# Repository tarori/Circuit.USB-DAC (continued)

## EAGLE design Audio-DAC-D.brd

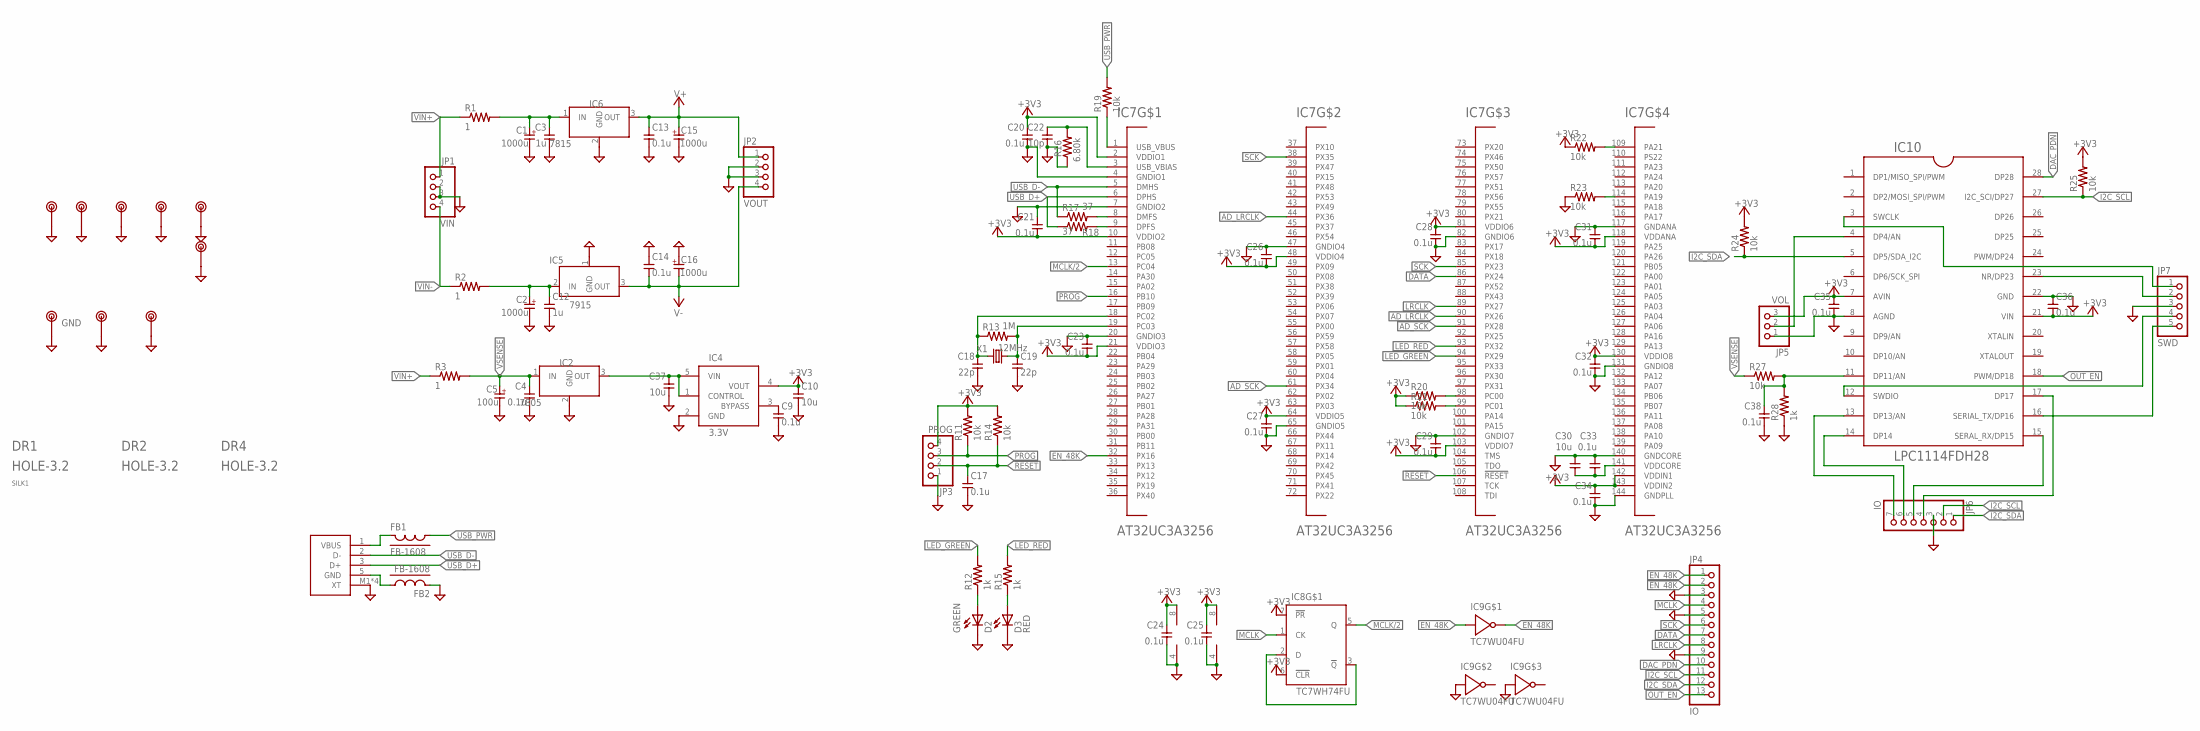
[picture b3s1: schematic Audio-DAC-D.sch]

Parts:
C1, C2, C15, C16: 1000u; E5-10
C3, C12: 1u; 1608
C4, C9, C17, C20, C21, C23, C24, C25, C26, C27, C28, C29, C31, C32, C33, C34, C35, C36, C38: 0.1u; 1608
C5: 100u; E2.5-6.5
C10, C30, C37: 10u; 2012
C13, C14: 0.1u; 2012
C18, C19: 22p; 1608
C22: 10p; 1608
CON1: USB; UX60A-MB-5ST
D2: GREEN; D1608
D3: RED; D1608
DR1, DR2, DR4: HOLE-3.2; HOLE_3.2
FB1, FB2: FB-1608; 1608
IC2: 7805; 7805-LARGEHOLE
IC4: 3.3V; SOT23-5
IC5: 7915; 7805-LARGEHOLE
IC6: 7815; 7805-LARGEHOLE
IC7: AT32UC3A3256; TQFP144
IC8: TC7WH74FU; SSOP8-P-0.65
IC9: TC7WU04FU; SSOP8-P-0.65
IC10: LPC1114FDH28; TSSOP28
JP1: VIN; 1X04
JP2: VOUT; 1X04
JP3: PROG; 1X04
JP4: IO; 1X13
JP5: VOL; 1X03
JP6: IO; 1X07
JP7: SWD; 1X05
R1, R2, R3: 1; 0204/7
R11, R14, R19, R20, R21, R22, R23, R24, R25, R27: 10k; 1608
R12, R15, R28: 1k; 1608
R13: 1M; 0204/7
R16: 6.80k; 1608
R17, R18: 37; 1608
SILK1: ROBOTECHWHEELSILK-9MM; ROBOTECHWHEEL-9MM
TP1, TP3, TP4, TP5, TP6, TP7, TP8, TP9: TESTPIN
TP2: GND; TESTPIN
X1: 12MHz; HC49/S

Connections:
!EN_48K: IC9.7, JP4.2
!RESET: C17.1, IC7.106 (!RESET), JP3.2, R14.1
+3V3: C10.1, C20.1, C21.2, C23.2, C24.1, C25.1, C26.2, C27.1, C28.1, C29.2, C31.2, C32.1, C34.1, C35.1, C36.2, IC4.4 (VOUT), IC7.2 (VDDIO1), IC7.10 (VDDIO2), IC7.21 (VDDIO3), IC7.48 (VDDIO4), IC7.64 (VDDIO5), IC7.81 (VDDIO6), IC7.103 (VDDIO7), IC7.118 (VDDANA), IC7.130 (VDDIO8), IC7.142 (VDDIN1), IC7.143 (VDDIN2), IC8.6 (!CLR), IC8.7 (!PR), IC8.8 (V+), IC9.8 (V+), IC10.7 (AVIN), IC10.21 (VIN), JP3.4, JP5.3, R11.2, R14.2, R20.1, R21.1, R22.1, R24.2, R25.2
AD_LRCLK: IC7.44 (PX36), IC7.90 (PX26)
AD_SCK: IC7.61 (PX34), IC7.91 (PX28)
DAC_PDN: IC10.28 (DP28), JP4.10
DATA: IC7.86 (PX24), JP4.7
EN_48K: IC7.32 (PX16), IC9.1, JP4.1
GND: C1.- (2), C2.- (2), C3.2, C4.2, C5.- (2), C9.2, C10.2, C12.2, C13.2, C14.1, C15.- (2), C16.+ (1), C17.2, C18.2, C19.2, C20.2, C21.1, C22.2, C23.1, C24.2, C25.2, C26.1, C27.2, C28.2, C29.1, C30.1, C31.1, C32.2, C33.1, C34.2, C35.2, C36.1, C37.2, C38.2, CON1.M1 (XT), CON1.M2 (XT), CON1.M3 (XT), CON1.M4 (XT), D2.K, D3.K, FB2.2, IC2.2 (GND), IC4.2 (GND), IC5.1 (GND), IC6.2 (GND), IC7.4 (GNDIO1), IC7.7 (GNDIO2), IC7.20 (GNDIO3), IC7.47 (GNDIO4), IC7.65 (GNDIO5), IC7.82 (GNDIO6), IC7.102 (GNDIO7), IC7.117 (GNDANA), IC7.131 (GNDIO8), IC7.140 (GNDCORE), IC7.144 (GNDPLL), IC8.4 (V-), IC9.3, IC9.4 (V-), IC9.6, IC10.8 (AGND), IC10.22 (GND), JP1.2, JP1.3, JP2.2, JP2.3, JP3.1, JP4.3, JP4.5, JP4.9, JP5.1, JP6.3, JP7.3, R16.1, R23.1, R28.1, TP1.1, TP2.1, TP3.1, TP4.1, TP5.1, TP6.1, TP7.1, TP8.1, TP9.1
I2C_SCL: IC10.27 (I2C_SCI/DP27), JP4.11, JP6.2, R25.1
I2C_SDA: IC10.5 (DP5/SDA_I2C), JP4.12, JP6.1, R24.1
LED_GREEN: IC7.94 (PX29), R12.2
LED_RED: IC7.93 (PX32), R15.2
LRCLK: IC7.89 (PX27), JP4.8
MCLK: IC8.1 (CK), JP4.4
MCLK/2: IC7.13 (PC04), IC8.5 (Q)
unnamed: CON1.5 (GND), FB2.1
unnamed: IC10.4 (DP4/AN), JP5.2
unnamed: C9.1, IC4.3 (BYPASS)
unnamed: C37.1, IC2.3 (OUT), IC4.1 (CONTROL), IC4.5 (VIN)
unnamed: IC7.9 (DPFS), R18.2
unnamed: IC7.8 (DMFS), R17.2
unnamed: C22.1, IC7.3 (USB_VBIAS), R16.2
unnamed: C19.1, IC7.19 (PC03), R13.2, X1.1
unnamed: C18.1, IC7.18 (PC02), R13.1, X1.2
unnamed: IC7.109 (PA21), R22.2
unnamed: IC7.114 (PA19), R23.2
unnamed: C38.1, IC10.11 (DP11/AN), R27.2, R28.2
unnamed: IC7.99 (PC01), R21.2
unnamed: IC7.98 (PC00), R20.2
unnamed: C30.2, C33.2, IC7.141 (VDDCORE)
unnamed: C1.+ (1), C3.1, IC6.1 (IN), R1.2
unnamed: C2.+ (1), C12.1, IC5.2 (IN), R2.2
unnamed: IC7.1 (USB_VBUS), R19.1
unnamed: IC8.2 (D), IC8.3 (!Q)
unnamed: D2.A, R12.1
unnamed: D3.A, R15.1
unnamed: IC10.3 (SWCLK), JP7.1
unnamed: IC10.23 (NR/DP23), JP7.2
unnamed: IC10.12 (SWDIO), JP7.4
unnamed: IC10.16 (SERIAL_TX/DP16), JP7.5
unnamed: IC10.13 (DP13/AN), JP6.7
unnamed: IC10.14 (DP14), JP6.6
unnamed: IC10.15 (SERAL_RX/DP15), JP6.5
unnamed: IC10.17 (DP17), JP6.4
OUT_EN: IC10.18 (PWM/DP18), JP4.13
PROG: IC7.16 (PB10), JP3.3, R11.1
SCK: IC7.38 (PX35), IC7.85 (PX23), JP4.6
USB_D+: CON1.3 (D+), IC7.6 (DPHS), R18.1
USB_D-: CON1.2 (D-), IC7.5 (DMHS), R17.1
USB_PWR: FB1.1, R19.2
V+: C13.1, C15.+ (1), IC6.3 (OUT), JP2.1
V-: C14.2, C16.- (2), IC5.3 (OUT), JP2.4
VBUS: CON1.1 (VBUS), FB1.2
VIN+: JP1.1, R1.1, R3.1
VIN-: JP1.4, R2.1
VSENSE: C4.1, C5.+ (1), IC2.1 (IN), R3.2, R27.1

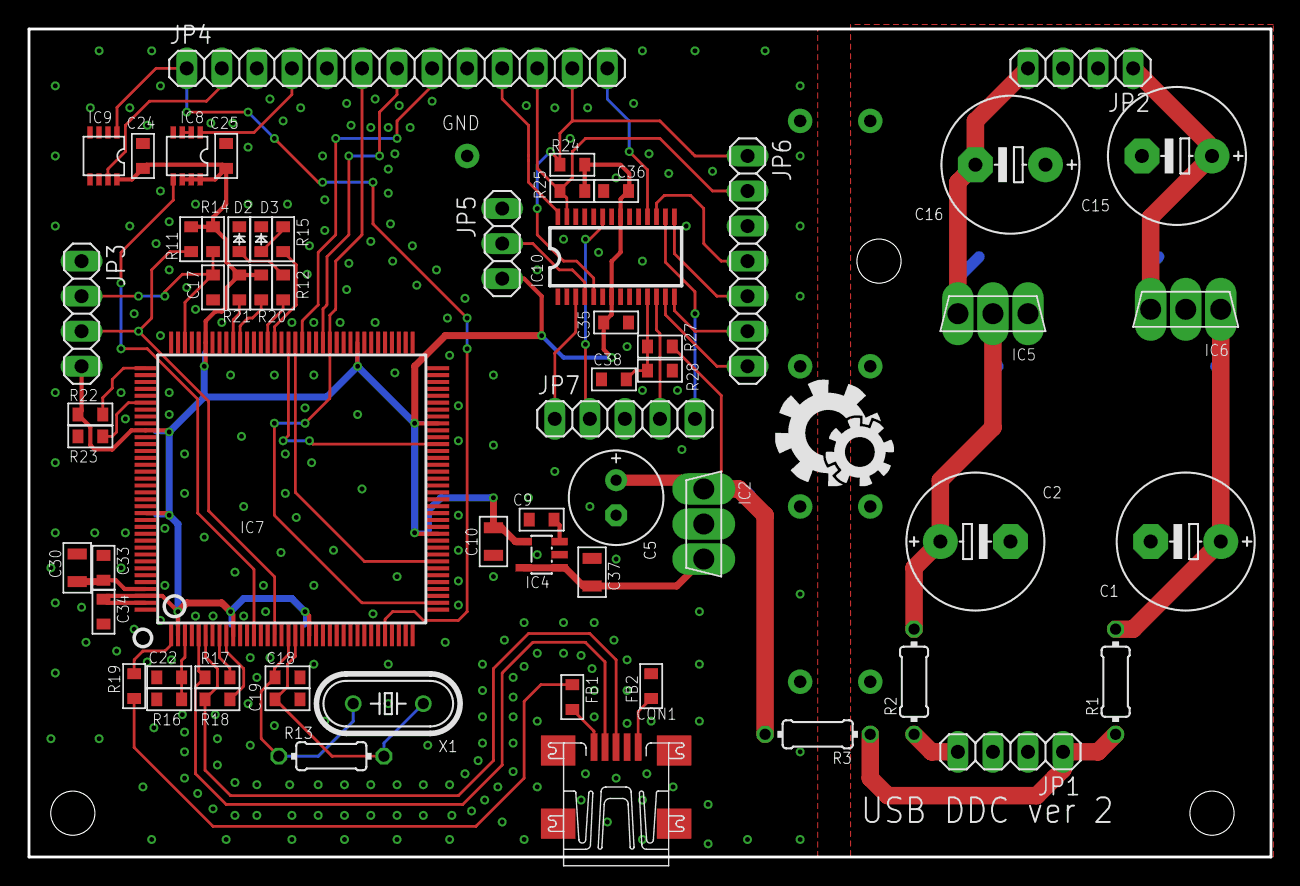
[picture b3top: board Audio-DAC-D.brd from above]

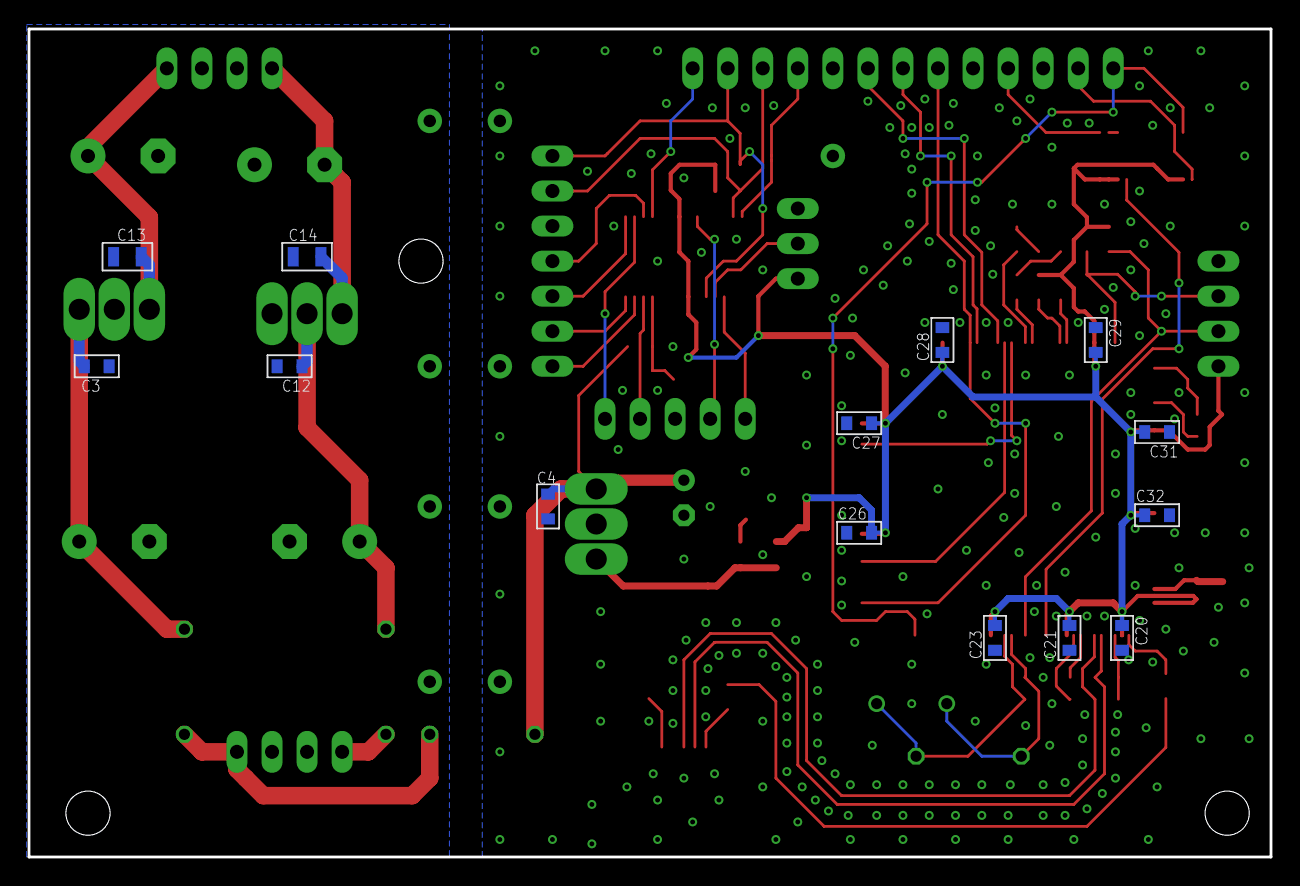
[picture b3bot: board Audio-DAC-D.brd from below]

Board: 2 copper layers, 90.0 x 60.0 mm, 88 parts (14 on the bottom side), 57 nets.

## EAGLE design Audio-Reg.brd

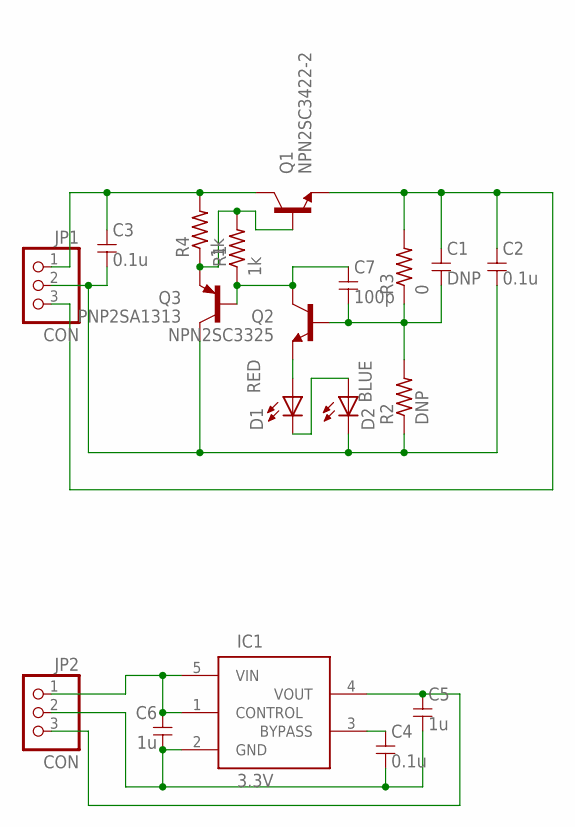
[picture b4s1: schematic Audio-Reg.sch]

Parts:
C1: DNP; 1608
C2, C3, C4: 0.1u; 1608
C5, C6: 1u; 1608
C7: 100p; 1608
D1: RED; D1608
D2: BLUE; D1608
IC1: 3.3V; SOT23-5
JP1, JP2: CON; 1X03
Q1: NPN2SC3422-2; TO126-2
Q2: NPN2SC3325; SC59
Q3: PNP2SA1313; SC59
R1, R4: 1k; 1608
R2: DNP; 1608
R3: 0; 1608

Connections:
GND: C2.2, C3.2, D2.K, JP1.2, Q3.3 (C), R2.1
IN: C3.1, JP1.1, Q1.2 (C), R4.2
unnamed: Q1.3 (B), Q3.2 (E), R1.2, R4.1
unnamed: D1.K, D2.A
unnamed: C1.2, C7.2, Q2.1 (B), R2.2, R3.1
unnamed: D1.A, Q2.2 (E)
unnamed: C4.1, IC1.3 (BYPASS)
unnamed: C4.2, C5.2, C6.2, IC1.2 (GND), JP2.2
unnamed: C6.1, IC1.1 (CONTROL), IC1.5 (VIN), JP2.1
unnamed: C5.1, IC1.4 (VOUT), JP2.3
unnamed: C7.1, Q2.3 (C), Q3.1 (B), R1.1
OUT: C1.1, C2.1, JP1.3, Q1.1 (E), R3.2

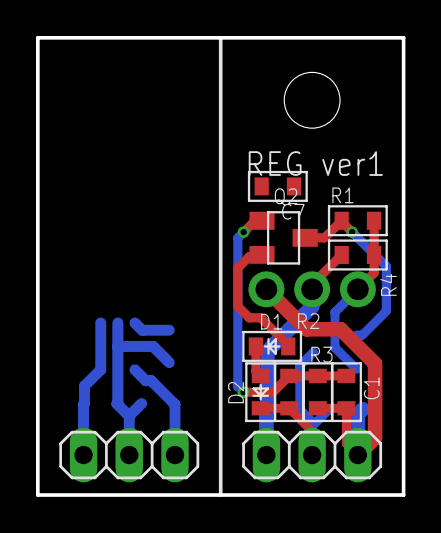
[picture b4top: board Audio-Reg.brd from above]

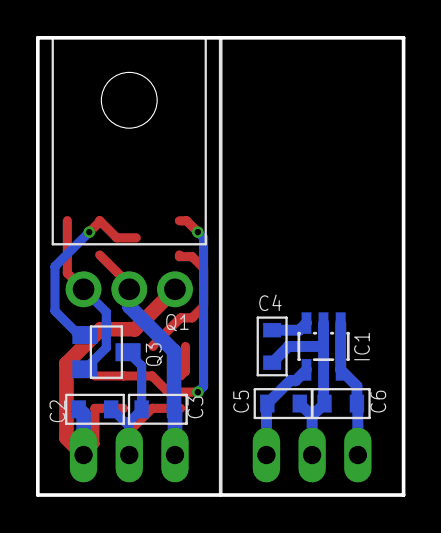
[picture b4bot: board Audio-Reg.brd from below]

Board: 2 copper layers, 20.3 x 25.4 mm, 19 parts (8 on the bottom side), 12 nets.

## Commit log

2020-02-24 回路図完成
2020-02-24 HPA強化
2020-03-17 tiny change
2020-04-30 Vカット
2020-06-19 回路図を修正
2020-07-10 デジタル部の回路図
2020-07-11 アイソレーター追加
2020-07-12 デジタル部配置
2020-07-12 Add README
2020-07-13 べた以外できた
2020-07-13 DDCのフォトカプラ追加
2020-07-14 ほぼ完成
2020-07-15 ビアを打った
2020-07-15 フォトカプラを反転
2020-07-15 アイソレーターをsi8420に
2020-07-16 fix readme
2020-08-12 Change to AK4493
2020-08-13 大体できた
2020-08-13 シルク調整
2021-03-09 AK4490
2021-03-09 PCM1795途中
2021-03-16 だいたい
2021-03-16 全部つないだ
2021-03-16 バージョン
2021-03-16 シルク整えた
2021-03-16 Add 位相補償
2021-04-17 fix PCM1795
2021-08-25 AK4495に変える
2022-03-17 ヒートシンクつけた
2022-03-18 LPF追加
2022-03-20 AK4493に
2022-12-17 LPF強化&発振対策
2023-08-18 AK1110に変更中
2024-09-21 バッファ改良
